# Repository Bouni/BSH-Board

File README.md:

# BSH-Board

This project is one of many variants of a PCB that can be used to interface with B/S/H appliances using the awsome [bsh-home-appliances](https://github.com/hn/bsh-home-appliances) project.

# Warning
> [!WARNING]
> Household appliances work with high voltages and currents. They generate heat and steam, they shake, vibrate and have rotating parts. You should have a good knowledge of electrics and take appropriate safety measures before opening or modifying such an appliance. Parts can get wet or hot, move or fall off.

> [!WARNING]
> Even if parts of the appliances operate at low voltages, depending on your specific model they may or may not be isolated from earth. This is a good chance of death or serious injury.
> I'm not responsible if you kill your cat, your spouse, your favourite pet fish, or yourself, whichever of these is the worst for you. You have been warned.

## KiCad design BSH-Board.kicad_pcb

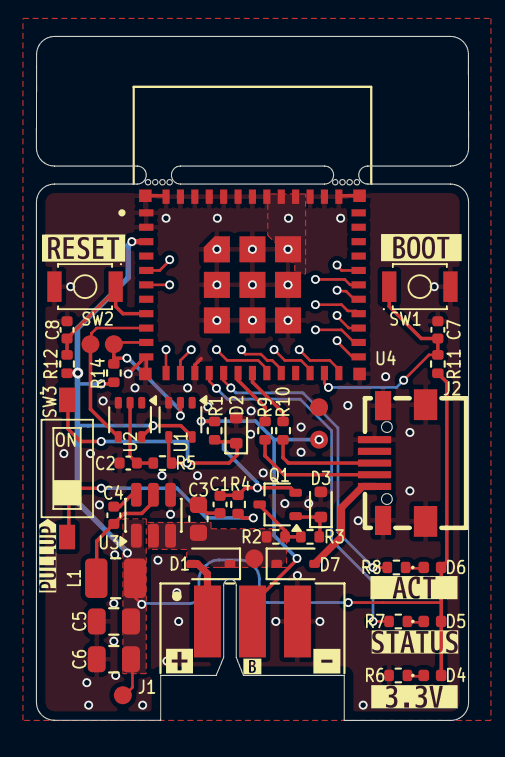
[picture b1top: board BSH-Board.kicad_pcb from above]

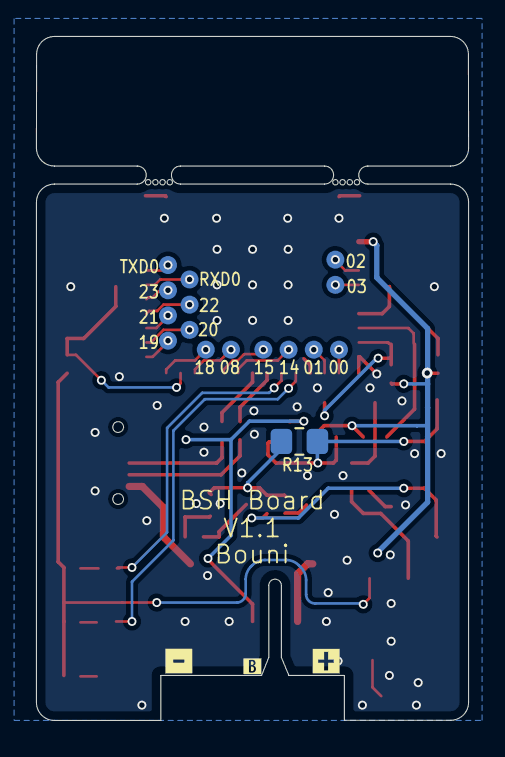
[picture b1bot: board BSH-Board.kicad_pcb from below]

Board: 2 copper layers, 24.0 x 38.0 mm, 73 parts (19 on the bottom side), 42 nets.

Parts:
C1, C4, C7, C8: 100nF; C_0402_1005Metric
C2: 1nF; C_0402_1005Metric
C3: 10uF; C_0603_1608Metric
C5, C6: 22uF; C_0805_2012Metric
D1, D7: 1N5819WS; D_SOD-323
D2, D3: BZX584C5V6; D_SOD-523
D4: LED_R; LED_0402_1005Metric
D5: LED_G; LED_0402_1005Metric
D6: LED_B; LED_0402_1005Metric
J1: 667101210103; J_Wurth_WR-RAST_667101230103
J2: MICRO QTZB5.0; MICRO-USB-SMD_MICRO-QTZB5.0
L1: 3.3uH; L_1008_2520Metric
Q1: MMST3904; SOT-323_SC-70
R1: 100; R_0402_1005Metric
R2, R5: 1K; R_0402_1005Metric
R3: 100K; R_0402_1005Metric
R4, R11, R12, R14: 10k; R_0402_1005Metric
R6, R7, R8: 510; R_0402_1005Metric
R9, R10: 22; R_0402_1005Metric
R13: ?k; R_0805_2012Metric_Pad1.20x1.40mm_HandSolder
SW1, SW2: TS-3025-B-C-B; SW-SMD_L3.0-W2.5-P3.40-LS4.0-L
SW3: SW_DIP_x01; SW-SMD_DSHP01TSGER
TP1, TP2, TP3, TP4, TP5, TP6, TP7, TP8, TP9, TP10, TP11, TP12, TP13, TP14, TP15, TP16, TP17, TP18, TP19, TP20, TP21: TestPoint; TestPoint_Pad_D1.0mm
U1: 74LVC1G07; SOT-353_SC-70-5
U2: 74LVC1G17; SOT-353_SC-70-5
U3: AP63203WU; TSOT-23-6
U4: ESP32-C6-MINI-1-N4; XCVR_ESP32-C6-MINI-1-N4
kibuzzard-69A53AD7: G***; kibuzzard-69A53AD7
kibuzzard-69A53AE7: G***; kibuzzard-69A53AE7
kibuzzard-69A53B6F: G***; kibuzzard-69A53B6F
kibuzzard-69A53B23: G***; kibuzzard-69A53B23
kibuzzard-69A53B53: G***; kibuzzard-69A53B53
kibuzzard-69A53BB2, kibuzzard-69A53BB2#2: G***; kibuzzard-69A53BB2
kibuzzard-69A53BC4, kibuzzard-69A53BC4#2: G***; kibuzzard-69A53BC4
kibuzzard-69A53BD0, kibuzzard-69A53BD0#2: G***; kibuzzard-69A53BD0
kibuzzard-69A53C55: G***; kibuzzard-69A53C55

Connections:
+3.3V: C5.1, C6.1, D4.2 (A), D5.2 (A), D6.2 (A), L1.2, R11.2, R12.2, R14.2, TP6.1, U1.5 (VCC), U2.5 (VCC), U3.1 (FB), U4.3 (3V3)
ACTIVITY: R8.1, U4.16 (IO7)
BOOT: C7.1, R11.1, SW1.1, U4.23 (IO9)
DBUS-RX: TP4.1, U2.4, U4.9 (IO4)
DBUS-TX: R14.1, TP3.1, U1.2, U4.10 (IO5)
GND: C1.1, C2.1, C3.2, C5.2, C6.2, C7.2, C8.2, D2.2 (A), D3.2 (A), J1.A3, J2.5 (GND), J2.6 (Shield), R6.1, SW1.2, SW2.2, TP1.1, U1.3 (GND), U2.3 (GND), U3.4 (GND), U4.1 (GND1), U4.2 (GND1), U4.11 (GND1), U4.14 (GND1), U4.36 (GND1), U4.37 (GND1), U4.38 (GND1), U4.39 (GND1), U4.40 (GND1), U4.41 (GND1), U4.42 (GND1), U4.43 (GND1), U4.44 (GND1), U4.45 (GND1), U4.46 (GND1), U4.47 (GND2), U4.48 (GND2), U4.49_1 (GND2), U4.49_2 (GND2), U4.49_3 (GND2), U4.49_4 (GND2), U4.49_5 (GND2), U4.49_6 (GND2), U4.49_7 (GND2), U4.49_8 (GND2), U4.49_9 (GND2), U4.50 (GND2), U4.51 (GND2), U4.52 (GND2), U4.53 (GND2)
unnamed: C2.2, R5.1, U2.2
unnamed: D1.2 (A), J1.A1
unnamed: D2.1 (K), R1.1, R5.2, R13.1, SW3.1, U1.4
unnamed: D3.1 (K), Q1.1 (B), R3.1
unnamed: D4.1 (K), R6.2
unnamed: D5.1 (K), R7.2
unnamed: D6.1 (K), R8.2
unnamed: D7.2 (A), J2.1 (VBUS)
unnamed: J1.A2, R1.2, TP2.1
unnamed: Q1.3 (C), R2.1, R3.2
unnamed: C1.2, Q1.2 (E), R4.2, R13.2
unnamed: R4.1, SW3.2
unnamed: C4.2, U3.6 (BST)
unnamed: C4.1, L1.1, U3.5 (SW)
unnamed: TP7.1, U4.12 (IO0)
unnamed: TP8.1, U4.13 (IO1)
unnamed: TP9.1, U4.5 (IO2)
unnamed: TP10.1, U4.6 (IO3)
unnamed: TP11.1, U4.22 (IO8)
unnamed: R9.1, U4.17 (IO12)
unnamed: R10.1, U4.18 (IO13)
unnamed: TP14.1, U4.19 (IO14)
unnamed: TP15.1, U4.20 (IO15)
unnamed: TP16.1, U4.24 (IO18)
unnamed: TP17.1, U4.25 (IO19)
unnamed: TP18.1, U4.26 (IO20)
unnamed: TP19.1, U4.27 (IO21)
unnamed: TP20.1, U4.28 (IO22)
unnamed: TP21.1, U4.29 (IO23)
unnamed: TP13.1, U4.30 (RXD0)
unnamed: TP12.1, U4.31 (TXD0)
RESET: C8.1, R12.1, SW2.1, U4.8 (EN)
STATUS: R7.1, U4.15 (IO6)
USB-D+: J2.3 (D+), R10.2
USB-D-: J2.2 (D-), R9.2
VCC: C3.1, D1.1 (K), D7.1 (K), R2.2, TP5.1, U3.2 (EN), U3.3 (IN)

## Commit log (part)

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2025-12-30 Quick and dirty draft
2025-12-30 Add LDO for 5V
2026-01-05 Added USB, replaced various parts
2026-01-05 Added LCSC numbers, replaced parts with Basic parts, added LEDs
2026-01-06 Minor improvements
2026-01-06 Clenaupo
2026-01-06 First attempt to auto generate Releases
2026-01-06 Next attempt to fix GH action
2026-01-06 Almost there
2026-01-06 Trigger CI
2026-01-06 Fix German artifacts
2026-01-06 Quick test for GH API
2026-01-06 One more
2026-01-06 And one more
2026-01-06 Fingers crossed
2026-01-06 Minor improvements to the Auto Release Action
2026-01-06 Little fix
2026-01-06 Next attempt to generate a step file
2026-01-06 And another one
2026-01-07 Next attempt
2026-01-07 next
2026-01-07 debugging ...
2026-01-07 One more try
2026-01-07 Simplify action
2026-01-07 Update README for pre-release 1.0-RC1
2026-01-07 Cleanup
2026-01-07 Fixed some issues, added missing JLC part numbers
2026-01-07 More cleanup
2026-01-07 Add script to run and debug kibot locally, slim donw kibot config, add JLC rotation corrections
2026-01-07 Redo V1.0-RC1
2026-01-07 Added an ESPHome config, still a draft, not sure if it works
2026-01-16 Fix TXS0102DQER bug
2026-01-16 Adjusted resistor values for green and blue led
2026-01-20 TXS0102 OE directly to 3.3v, all spare IOs to Testpoints
2026-01-20 Removed bottom pads of RAST connector
2026-01-20 Replaced TXS0102 with Pullup + 74LVC1G07 + Zener
2026-01-21 Went back to LSF0102
2026-01-22 Using 74LVC Logic, get rid of LDO for 5V
2026-01-22 Finished layout
2026-02-06 Extended board to reach under the antenna
2026-02-16 V1.0 with antenna cutout
2026-02-16 Add 3D models for a case for V1.0-RC2
2026-02-16 Fixed issue with lid clamping
2026-02-16 Add modified case version for V1.0
2026-02-16 Add RAST coding notch
2026-02-27 Add dip switch for pullup, add TX pullup, add empty 0805 for potential other pullup value
2026-03-02 Various minor improvements
2026-03-02 Put V-Cut into seperate layer
2026-03-02 Kibot V-Cuts test
2026-03-02 Fix typo
2026-03-02 Hopefully fixed output now
2026-03-18 Update bsh-dbus-wm14e3a0.yaml
    remove debug from uart
2026-03-20 Bump Version
2026-03-20 Replaced V-Cuts with Mousebites
2026-04-07 Remove output files
2026-04-07 Fix version
2026-04-07 Restore Kicad 9 Files as Kibot does not yet support Kicad 10
2026-04-07 Fix #3, Silkscreen on the bottom layer was wrong (+/-)
2026-04-21 Add Case and Lid for V1.1
2026-04-29 Add updated V1.1 Case files
2026-04-29 Add INFO.md to case files
